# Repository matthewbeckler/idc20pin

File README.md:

# idc20pin
Adapter board for IDC 20 pin connector

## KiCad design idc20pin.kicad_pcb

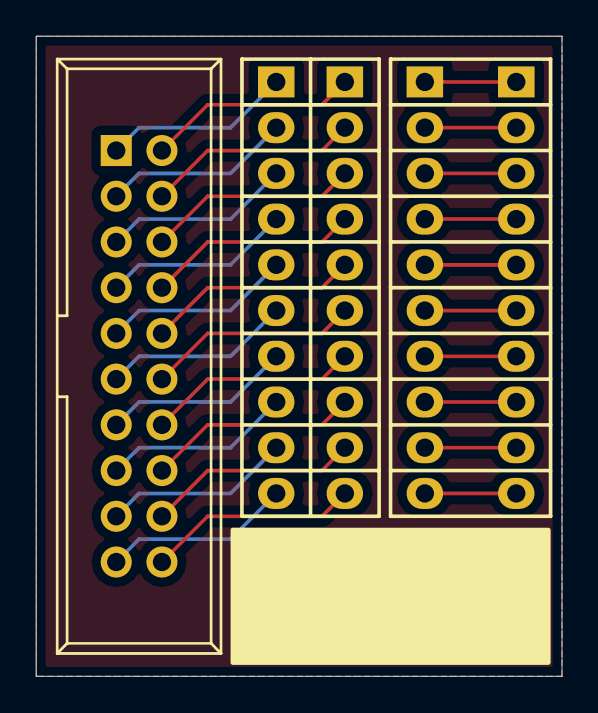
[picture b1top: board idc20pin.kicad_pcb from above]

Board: 2 copper layers, 29.2 x 35.6 mm, 5 parts (0 on the bottom side), 30 nets.

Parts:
P1: ARMJTAG20_IDC; IDC_Header_Straight_20pins
P2, P3, P4, P5: CONN_01X10; Pin_Header_Straight_1x10

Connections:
/N01: P1.1, P2.1
/N02: P1.2, P3.1
/N03: P1.3, P2.2
/N04: P1.4, P3.2
/N05: P1.5, P2.3
/N06: P1.6, P3.3
/N07: P1.7, P2.4
/N08: P1.8, P3.4
/N09: P1.9, P2.5
/N10: P1.10, P3.5
/N11: P1.11, P2.6
/N12: P1.12, P3.6
/N13: P1.13, P2.7
/N14: P1.14, P3.7
/N15: P1.15, P2.8
/N16: P1.16, P3.8
/N17: P1.17, P2.9
/N18: P1.18, P3.9
/N19: P1.19, P2.10
/N20: P1.20, P3.10
unnamed: P4.1, P5.1
unnamed: P4.2, P5.2
unnamed: P4.3, P5.3
unnamed: P4.4, P5.4
unnamed: P4.5, P5.5
unnamed: P4.6, P5.6
unnamed: P4.7, P5.7
unnamed: P4.8, P5.8
unnamed: P4.9, P5.9
unnamed: P4.10, P5.10

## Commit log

2017-01-11 i2c20pin adapter board v1
